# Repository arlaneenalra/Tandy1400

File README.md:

# Tandy1400 PSU

A very rough potential replacement for a Tandy 1400 PSU. At this point the board has not been tested 
in any way, shape, or form and is only published for potential review.

> [!CAUTION]
> **Do not use the 12V 1.2A power brick that comes with the Tandy 1400FD (Catalog Number 25-3501).**
> This power brick is a simple unregulated supply that may output much higher voltages than the rated 12v. The unit I examined would output 15.86v unloaded. The maximum input voltages for the MEZD41502A-C 15v DC-DC converter is 13v and I have no idea what would happen if it saw 15.86v instead.
>
> The power adapter from the 1400HD model (12v 2.2A Catalog Number 25-3505) appears to be better regulated and is what I've been using for testing.

## Status

2024-12-15 - Bug Fixes
* Upped C2 to 100uF, 47 seems to not quite be enough for the LCD to work well, you get some fading and potentially contrast issues.
* Ordered potentially replacement for the 15v DC-DC converter, if it works, I'll add the converter module to the repo and start an SMD version of the board.

2024-12-01 - Bug fixes
* This should finally fix the MEZD41502A-C footprint.
* Validated the board in "wall power only" configuration.
* At this point, the basic design has been shown to work. I'm not going to order more boards until I have a fix for the [availability issue](https://github.com/arlaneenalra/Tandy1400/issues/3).

2024-11-24 - Bug fixes
* Reversed the switch footprint. - Should orient the stock switch correctly now.
* Reversed the 15v converter and pulled in slightly from the edge of the board. This should avoid solder joints on the back of the module being too close to the shield.
* Adjusted the one mounting whole that was too close to the edge of the board.
* Added a 330uF capacitor to prevent switch induced voltage spikes from killing a TP5100 module.
* Adjusted the through holes for battery leads.

2024-11-23 - Next iteration of the board arrived
* Switch footprint works but is backwards to the original
* 15v converter still too close to the edge, needs to come in about 2~3mm
* -22v rail seems to go between -30v and -27v, need to adjust the values a bit.
* Battery wire holes are too small.
* USB connected to the Arduino Nano can feed power into the dc in bus. It won't feed into the USB connector because of a diode in the Nano, but could power the 15v converter off of the USB port, less than ideal.
* Hmm, cooked the charger board when tried to plug in while on battery power. Not sure why.

2024-11-16 - Regenerating PCB layout for new order.
* A whole bunch of minor changes that should fix the -22v boost converter.
* New switch foot print should allow for harvesting the original switch.
* Added jumpers for operation without the Arduino.
* Screw holes are now actually grounded.

2024-11-11 - Boards arrived!
* Fixed pin size and overall footprint on U2. The holes were too small and it was too close to the edge.
* Fixed diode pin sizes, I had DO-41 and the diodes are actually D201AD.
* The whole -22v boost converter doesn't work ....
* Fixed incorrect inductor connections for negative boost converter
* Fixed R6 and R4 being reversed.

2024-11-05 - Just ordered a set of boards via JLCPCB. I'll update when they are received and tested.

# Ordering Boards

I recommend 1.6mm boards with 2oz copper. The pre-generated gerbers should be sufficient.

# Solder Jumpers

## JP1 ALWAYS_ON_5 and JP3 MCU_POWER
In the original board, there is a 5V rail that listed as always on. If you cut the 2-1 configuration of these jumpers and resolder them in 2-3 the MCU is always powered and the 5_ALWAYS
rail is powered off of the MCUs internal 5V linear regulator. I do not recommend this configuration, it is present primarily for experimentation.

## JP3 LOW_BATT and JP4 REALLY_LOW_BATT
There are two stages to the Tandy 1400s low battery behavior. The original PSU pulls these pins to ground when the battery is seen as fully charged. If you want to run without an Arduino
just short these two jumpers and it should stop the machine from continuously reporting low battery.

# Parts List

## Required
* C1, C2 - 100uF 50V
* C3 - 220pf
* C4 - 0.1uF
* C5 - 22uF 25V
* C6, C9 - 10uF 50V
* C7 - 2.2uF 50V
* C8 - 0.22uF
* D2 - 31DQ06 - 3A Power Diode
* D3 - 1N5819 - Schottky DO15 40V 1A 150C - This is like way overrated. I've been semi-successful with a 1N4148.
* F1 - Keystone 3568 (Mini Automotive Fuse Holder) - https://www.digikey.com/en/products/detail/keystone-electronics/3568/2137306
* F1 - 3 Amp Mini Automotive fuse - 2 Amp may be acceptable
* J2 - CP-063AH-ND Barrel Jack Connector - https://www.digikey.com/en/products/detail/same-sky-formerly-cui-devices/pj-063ah/2161208  
* J3 - EHR-15 and 14 ASEHSEH22K152 Jumpers - If you have an existing supply, this can be harvested off the old one.
  * https://www.digikey.com/en/products/detail/jst-sales-america-inc/EHR-15/527237
  * https://www.digikey.com/en/products/detail/jst-sales-america-inc/ASEHSEH22K152/6009479
* L1 - 330uH Inductor
* R6 - 1k 1/4w
* R3 - 1 ohm 1/4w 
* R4 - 15k 1/4w
* RV1 - 4.7k Trimmer 3296Y-1-472 or equivalent - https://www.digikey.com/en/products/detail/bourns-inc/3296Y-1-472/2536015 you want one with the adjustment on top or facing to the outer edge of the board when installed.
* SW1 - Z4418-ND - https://www.digikey.com/en/products/detail/omron-electronics-inc-emc-div/A8L-21-12N2/1811713
  * I've adjusted the footprint so that it's theoretically possible to harvest the original if you have one.
  * You might be able to harvest the switch off you're old supply, but the foot print is slightly different.
* U1 - MC34063 in either PDIP-8 or SOIC-8 form.
* U2 - MEZD41502A-C - 15V DC/DC boost converter (Digikey says it's obsolete, manufacturer didn't last I checked.) - https://www.digikey.com/en/products/detail/monolithic-power-systems-inc/MEZD41502A-C/6823857
* U3 - MEZD72401A-G - Drop in replacement for a TO-220-3 LM7805 - https://www.digikey.com/en/products/detail/monolithic-power-systems-inc/MEZD72401A-G/6823842
  * This is a 7805 equivalent rated for 1A. You could theoretically put a 7805 here, but you'd need to keep in mind heat dissipation and efficiency.
  * An alternative https://www.digikey.com/en/products/detail/monolithic-power-systems-inc/MEZD71201A-G/6823821 Should also work, really, this just needs to handle the 15v input voltage, match the 7805 pin out, and support up to 1A load.
* U4 - LM340T-12 - Note: This is powered off of a 15V rail so you'll probably need an actual linear regulator.
  * DO NOT try to use an N7812-1PH in place of the LM340T-12, this part needs a minimum of 20V to produce a +12V supply and has been seen to dump 36V out when under-voltaged.
* U5 - N7812-1PH - +/- 12V DC/DC Converter Used to generate -12V, cannot be used for +12V with a 15V supply. - https://www.digikey.com/en/products/detail/mean-well-usa-inc/N7812-1PH/22119016 
  * Keep a close eye on the pin-out for this one, the inductor goes down to match the board wiring. If installed incorrectly, the regulator is effectively dead.

## Suggested
* 3x TO-220 mounting kit - Something like https://www.digikey.com/en/products/detail/boyd-laconia-llc/4880SG/1625671
  * You may also want a bit of thermal compound (non-conductive).
  * None of the TO-220 parts should produce much heat so this may not strictly be necessary.
  * The N7812-1PH does not have a mounting hole.
  * The MEZD72401A-G uses 2.54mm header pins which are extremely difficult to bend. The board is laid out to allow it to be mounted to the board, but you may also need a small TO-220 heatsink similar to https://www.digikey.com/en/products/detail/cts-thermal-management-products/PB1-36CB/272680

* Multi-colored heatshrink tubing small diameter - If you are not harvesting the power lead off of an existing PSU board, this will help you distinguish which lead is witch in the JST connector.

## Optional
* A1 - 5v Arduino Nano (ATmega 328p based was used in prototype)
  * 2.54mm pin heade for the Arduino (28 pins)
  * R7, R9 - 150k 1/4w
  * R5, R8 - 200k 1/4w

* Battery Power
  * J1 - Jumper lead for battery connection. Size to match pack but should be able to handle at least 2A. (Through holes are sized for 18guage)
  * D1 - 31DQ06 - 3A Power Diode
  * D5 - 1N5819 - Schottky DO15 40V 1A 150C - This is like way overrated. I've been semi-successful with a 1N4148.
  * Q1 - IRF9540N P-Channel MOSFET in TO-220-3 - http://www.irf.com/product-info/datasheets/data/irf9540n.pdf
  * R1 - 1k 1/4w
  * R2 - 10k 1/4w
  * 2s Li-ion pack in the 3000mah range  - *Must have protection circuits* I would recommend 18650 based packs over Li-poly.
    * The current design uses a voltage divider at the Arduino. This could create a phantom load on the battery and drain it overtime.

* Charging - Experimental - *use at your own risk*
  * **WARNING: Cheap TP5100 charging modules have a high unexpected failure rate. If you do set this up, do not leave unattended while the machine is plugged in.**
  * D4 - 31DQ06 - Diode - D4 may just be a jumper, my TP5100 modules didn't like being connected to the battery unpowered.
  * U6 - TP5100 Charging module - https://www.amazon.com/Charging-Management-Voltage-Regulator-Batteries/dp/B0C781VGYY
    * It is recommended to remove one of the R100 resistors to drop to 1A charging.
  * C10 - 330uF 25v - The cheap TP5100 modules I've been using tend to blow up on voltage spikes without this.

* Note: Resistor wattage ratings are currently and estimate.

# References
* https://forum.vcfed.org/index.php?threads/tandy-1400-any-varients-with-hdd-expansion-slots-please-help.35455/page-2
* https://forum.vcfed.org/index.php?threads/dc-dc-converter-modules.1250102/
* https://www.lo-tech.co.uk/wiki/Tandy_1400FD
* [PSU Pinouts](https://docs.google.com/spreadsheets/d/1nll-RFp76xCkyXyzz_ilaRExv62mEH7IuoLMoUgfZ3Y/edit?usp=sharing)

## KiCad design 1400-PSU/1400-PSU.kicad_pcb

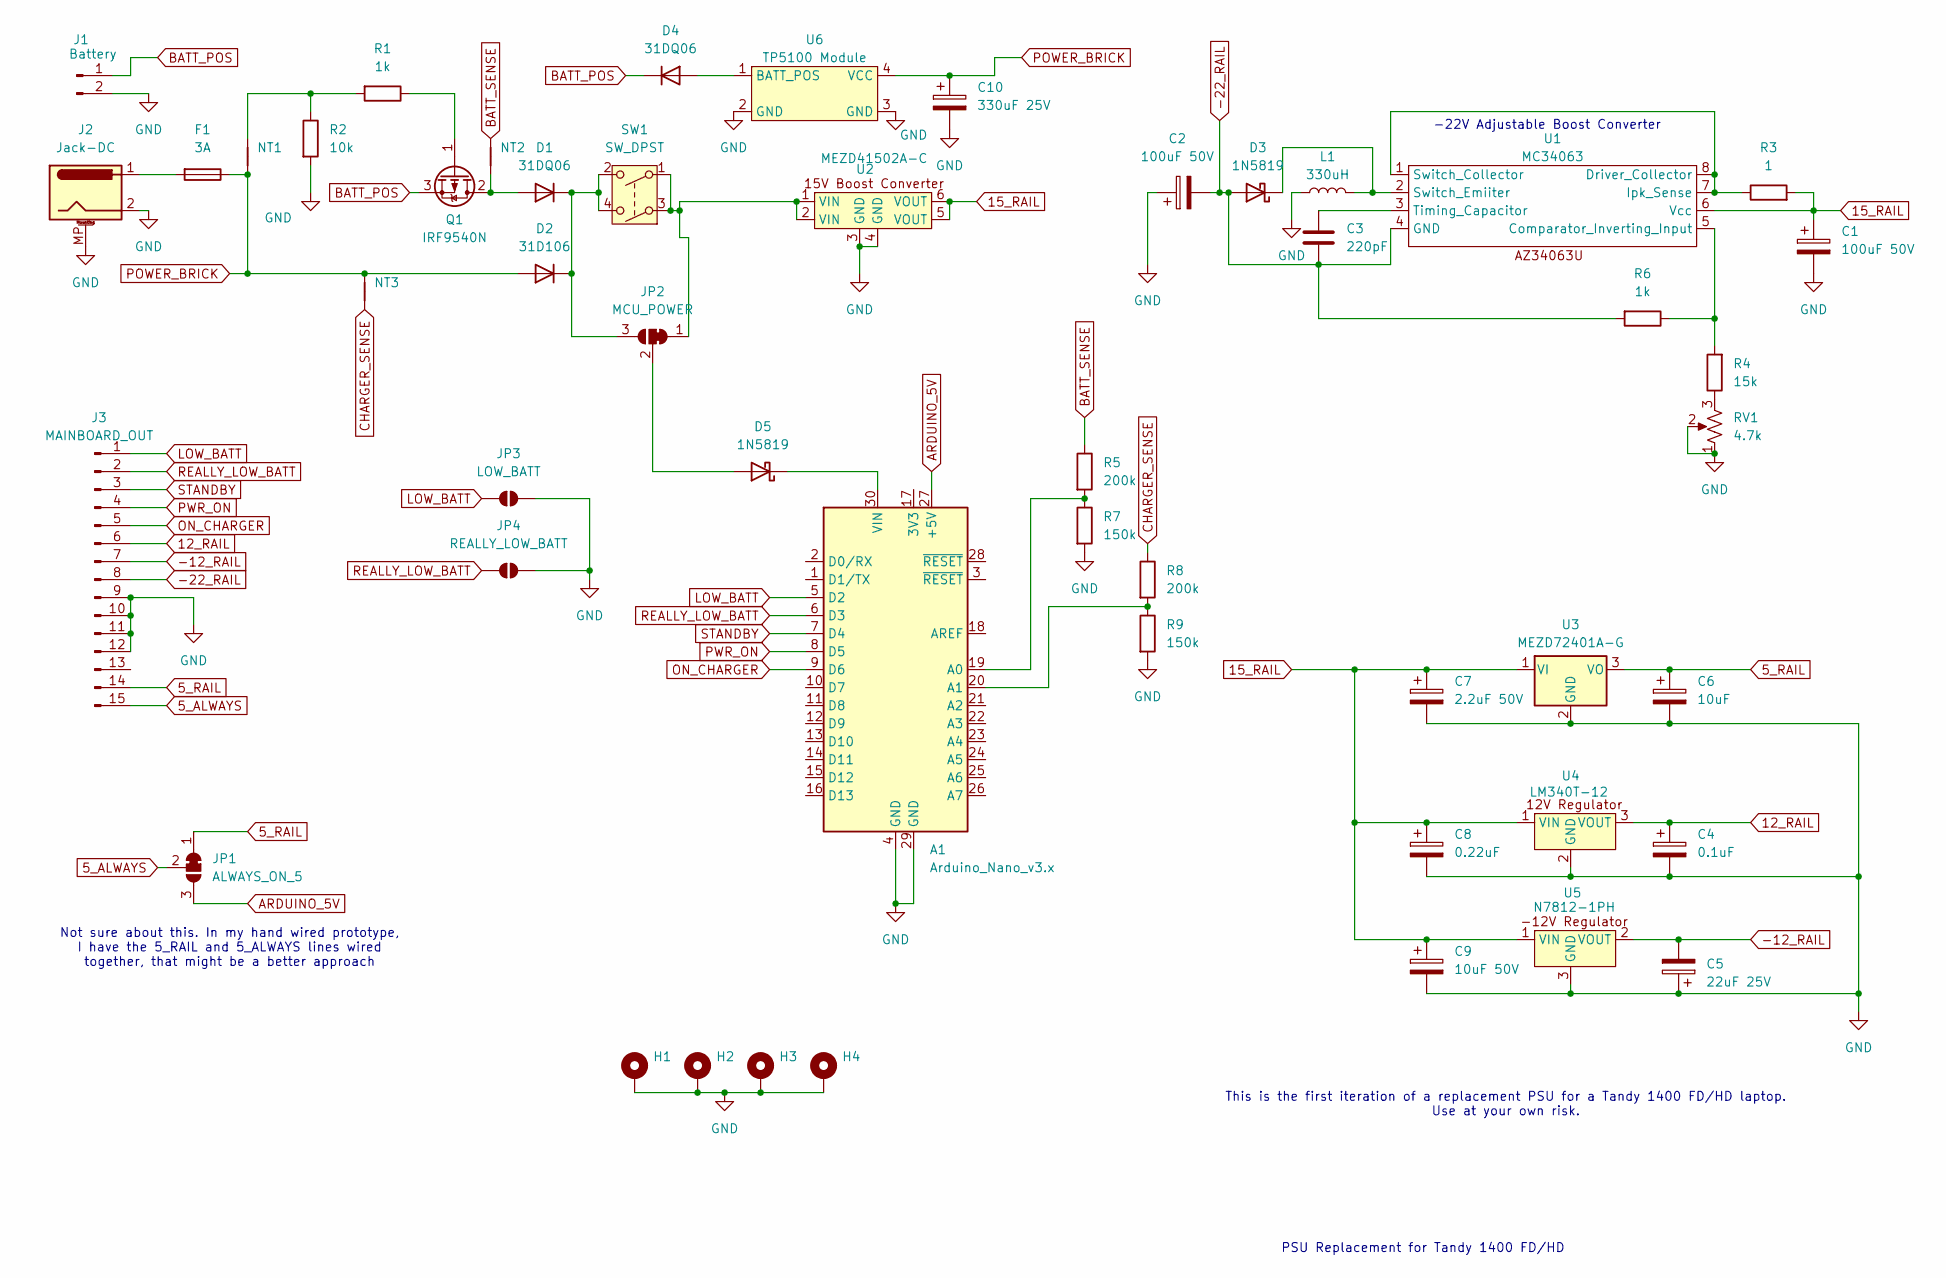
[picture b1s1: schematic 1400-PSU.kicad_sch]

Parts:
A1: Arduino_Nano_v3.x; Arduino_Nano
C1: 100uF 50V; CP_Radial_D8.0mm_P3.50mm
C2: 100uF 50V; CP_Radial_D10.0mm_P5.00mm
C3: 220pF; C_Disc_D5.1mm_W3.2mm_P5.00mm
C4: 0.1uF; C_Disc_D5.1mm_W3.2mm_P5.00mm
C5: 22uF 25V; CP_Radial_D6.3mm_P2.50mm
C6: 10uF; CP_Radial_D8.0mm_P5.00mm
C7: 2.2uF 50V; CP_Radial_D4.0mm_P2.00mm
C8: 0.22uF; C_Disc_D5.1mm_W3.2mm_P5.00mm
C9: 10uF 50V; CP_Radial_D8.0mm_P5.00mm
C10: 330uF 25V; CP_Radial_D8.0mm_P5.00mm
D1: 31DQ06; D_DO-201AD_P5.08mm_Vertical_AnodeUp
D2: 31D106; D_DO-201AD_P5.08mm_Vertical_KathodeUp
D3, D5: 1N5819; D_DO-41_SOD81_P10.16mm_Horizontal
D4: 31DQ06; D_DO-201AD_P12.70mm_Horizontal
F1: 3A; Fuseholder_Blade_Mini_Keystone_3568
H1, H2, H3, H4: MountingHole_3.5mm_Pad_TopBottom
J1: Battery; SolderWire-1.5sqmm_1x02_P7.8mm_D1.7mm_OD3.9mm
J2: Jack-DC; BarrelJack_CUI_PJ-063AH_Horizontal
J3: MAINBOARD_OUT; JST_EH_B15B-EH-A_1x15_P2.50mm_Vertical
JP1: ALWAYS_ON_5; SolderJumper-3_P1.3mm_Bridged12_RoundedPad1.0x1.5mm_NumberL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
JP2: MCU_POWER; SolderJumper-3_P1.3mm_Bridged12_RoundedPad1.0x1.5mm_NumberL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
JP3: LOW_BATT; SolderJumper-2_P1.3mm_Open_RoundedPad1.0x1.5mm
JP4: REALLY_LOW_BATT; SolderJumper-2_P1.3mm_Open_RoundedPad1.0x1.5mm
L1: 330uH; L_Radial_D8.7mm_P5.00mm_Fastron_07HCP
NT1, NT2, NT3: NetTie_2; NetTie-2_SMD_Pad2.0mm
Q1: IRF9540N; TO-220-3_Horizontal_TabDown
R1, R6: 1k; R_Box_L8.4mm_W2.5mm_P5.08mm
R2: 10k; R_Box_L8.4mm_W2.5mm_P5.08mm
R3: 1; R_Box_L8.4mm_W2.5mm_P5.08mm
R4: 15k; R_Box_L8.4mm_W2.5mm_P5.08mm
R5, R8: 200k; R_Box_L8.4mm_W2.5mm_P5.08mm
R7, R9: 150k; R_Box_L8.4mm_W2.5mm_P5.08mm
RV1: 4.7k; Potentiometer_Bourns_3299Y_Vertical
SW1: SW_DPST; A8L-21-12N2
U1: MC34063; SO_PDIP-8_3.9x4.9mm_P1.27mm_1
U2: MEZD41502A-C; Monolithic Power SIP6
U3: MEZD72401A-G; TO-220-3_Horizontal_TabDown
U4: LM340T-12; TO-220-3_Horizontal_TabDown
U5: N7812-1PH; TO-220-3_Horizontal_TabDown
U6: TP5100 Module; TP5100-Module

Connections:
5_ALWAYS: J3.15, JP1.2 (C)
5_RAIL: C6.1, J3.14, JP1.1 (A), U3.3 (VO)
12_RAIL: C4.1, J3.6, U4.3 (VOUT)
15_RAIL: C1.1, C7.1, C8.1, C9.1, R3.2, U1.6 (Vcc), U2.5 (VOUT), U2.6 (VOUT), U3.1 (VI), U4.1 (VIN), U5.1 (VIN)
-12_RAIL: C5.2, J3.7, U5.2 (VOUT)
-22_RAIL: C2.2, C3.2, D3.2 (A), J3.8, R6.2, U1.4 (GND)
ARDUINO_5V: A1.27 (+5V), JP1.3 (B)
BATT_POS: D4.1 (K), J1.1, Q1.3 (S)
BATT_SENSE: NT2.2, R5.1
CHARGER_SENSE: NT3.1, R8.1
GND: A1.4 (GND), A1.29 (GND), C1.2, C2.1, C4.2, C5.1, C6.2, C7.2, C8.2, C9.2, C10.2, H1.1, H2.1, H3.1, H4.1, J1.2, J2.2, J2.MP (MountPin), J3.9, J3.10, J3.11, J3.12, JP3.2 (B), JP4.2 (B), L1.1, R2.2, R7.2, R9.2, RV1.1, RV1.2, U2.3 (GND), U2.4 (GND), U3.2 (GND), U4.2 (GND), U5.3 (GND), U6.2 (GND), U6.3 (GND)
LOW_BATT: A1.5 (D2), J3.1, JP3.1 (A)
unnamed: A1.19 (A0), R5.2, R7.1
unnamed: A1.20 (A1), R8.2, R9.1
unnamed: A1.30 (VIN), D5.1 (K)
unnamed: D1.2 (A), NT2.1, Q1.2 (D)
unnamed: D1.1 (K), D2.1 (K), JP2.3 (B), SW1.2, SW1.4
unnamed: D3.1 (K), L1.2, U1.2 (Switch_Emiiter)
unnamed: D4.2 (A), U6.1 (BATT_POS)
unnamed: D5.2 (A), JP2.2 (C)
unnamed: F1.2, J2.1
unnamed: JP2.1 (A), SW1.1, SW1.3, U2.1 (VIN), U2.2 (VIN)
unnamed: NT1.2, R1.2, R2.1
unnamed: Q1.1 (G), R1.1
unnamed: R4.1, RV1.3
unnamed: R4.2, R6.1, U1.5 (Comparator_Inverting_Input)
unnamed: R3.1, U1.1 (Switch_Collector), U1.7 (Ipk_Sense), U1.8 (Driver_Collector)
unnamed: C3.1, U1.3 (Timing_Capacitor)
ON_CHARGER: A1.9 (D6), J3.5
POWER_BRICK: C10.1, D2.2 (A), F1.1, NT1.1, NT3.2, U6.4 (VCC)
PWR_ON: A1.8 (D5), J3.4
REALLY_LOW_BATT: A1.6 (D3), J3.2, JP4.1 (A)
STANDBY: A1.7 (D4), J3.3

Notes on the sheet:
This is the first iteration of a replacement PSU for a Tandy 1400 FD/HD laptop. Use at your own risk.
Not sure about this. In my hand wired prototype, I have the 5_RAIL and 5_ALWAYS lines wired together, that might be a better approach
-22V Adjustable Boost Converter
PSU Replacement for Tandy 1400 FD/HD

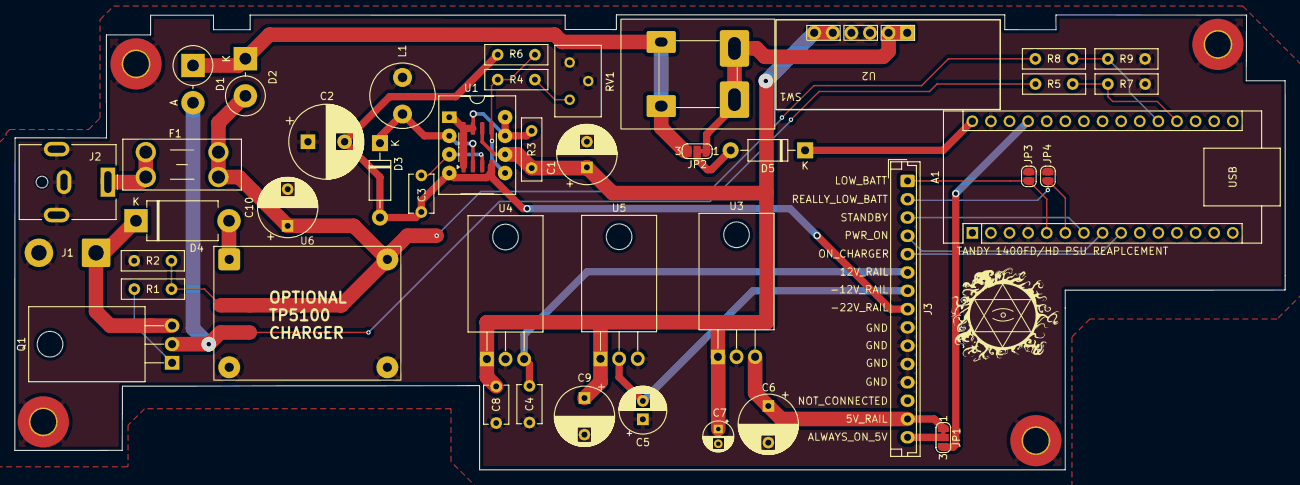
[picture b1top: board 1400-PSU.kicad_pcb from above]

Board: 2 copper layers, 173.4 x 62.1 mm, 50 parts (0 on the bottom side), 33 nets.

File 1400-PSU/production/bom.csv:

Designator,Footprint,Quantity,Value,LCSC Part #
A1,Arduino_Nano,1,Arduino_Nano_v3.x,
C1,CP_Radial_D8.0mm_P3.50mm,1,100uF 50V,
C10,CP_Radial_D8.0mm_P5.00mm,1,330uF 25V,
C2,CP_Radial_D10.0mm_P5.00mm,1,100uF 50V,
C3,C_Disc_D5.1mm_W3.2mm_P5.00mm,1,220pF,
C4,C_Disc_D5.1mm_W3.2mm_P5.00mm,1,0.1uF,
C5,CP_Radial_D6.3mm_P2.50mm,1,22uF 25V,
C6,CP_Radial_D8.0mm_P5.00mm,1,10uF,
C7,CP_Radial_D4.0mm_P2.00mm,1,2.2uF 50V,
C8,C_Disc_D5.1mm_W3.2mm_P5.00mm,1,0.22uF,
C9,CP_Radial_D8.0mm_P5.00mm,1,10uF 50V,
D1,D_DO-201AD_P5.08mm_Vertical_AnodeUp,1,31DQ06,
D2,D_DO-201AD_P5.08mm_Vertical_KathodeUp,1,31D106,
"D3, D5",D_DO-41_SOD81_P10.16mm_Horizontal,2,1N5819,
D4,D_DO-201AD_P12.70mm_Horizontal,1,31DQ06,
F1,Fuseholder_Blade_Mini_Keystone_3568,1,3A,
J1,SolderWire-1.5sqmm_1x02_P7.8mm_D1.7mm_OD3.9mm,1,Battery,
J2,BarrelJack_CUI_PJ-063AH_Horizontal,1,Jack-DC,
J3,JST_EH_B15B-EH-A_1x15_P2.50mm_Vertical,1,MAINBOARD_OUT,
L1,L_Radial_D8.7mm_P5.00mm_Fastron_07HCP,1,330uH,
Q1,TO-220-3_Horizontal_TabDown,1,IRF9540N,
"R1, R6",R_Box_L8.4mm_W2.5mm_P5.08mm,2,1k,
R2,R_Box_L8.4mm_W2.5mm_P5.08mm,1,10k,
R3,R_Box_L8.4mm_W2.5mm_P5.08mm,1,1,
R4,R_Box_L8.4mm_W2.5mm_P5.08mm,1,15k,
"R5, R8",R_Box_L8.4mm_W2.5mm_P5.08mm,2,200k,
"R7, R9",R_Box_L8.4mm_W2.5mm_P5.08mm,2,150k,
RV1,Potentiometer_Bourns_3299Y_Vertical,1,4.7k,
SW1,A8L-21-12N2,1,SW_DPST,
U1,SO_PDIP-8_3.9x4.9mm_P1.27mm_1,1,MC34063,
U2,Monolithic Power SIP6,1,MEZD41502A-C,
U3,TO-220-3_Horizontal_TabDown,1,MEZD72401A-G,
U4,TO-220-3_Horizontal_TabDown,1,LM340T-12,
U5,TO-220-3_Horizontal_TabDown,1,N7812-1PH,
U6,TP5100-Module,1,TP5100 Module,

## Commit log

2024-11-04 Inital import.
2024-11-05 Generated gerbers.
2024-11-16 Updating for next board revision.
2024-11-16 Update to readme and BOM.
2024-11-16 Generating new gerbers.
2024-11-16 Minor README updates.
2024-11-16 Update README.md
    Formatting fixes for Github markdown.
2024-11-23 Minor updates, still need to figure out the charging issue and move the 15v converter down.
2024-11-23 Nuke the old gerbers for now. I'll re-make them after the next update.
2024-11-23 Move one of the mounting holes a bit.
2024-11-24 Minor revisions.
2024-11-24 Generate new gerbers.
2024-11-24 Minor tweaks.
2024-12-01 Update README.md
    Add warning about the 1400FD power brick .. wow that scared me.
2024-12-02 Should fix #4.
2024-12-02 Fix readme typos
2024-12-05 Note about alternatives for the 5v regulator.
2024-12-05 KiCad updates.
2024-12-08 Adjust battery warning voltage dividers.
2024-12-08 Update to Arduino code.
2024-12-15 Minor update and fixes.
2024-12-17 resolve #6
